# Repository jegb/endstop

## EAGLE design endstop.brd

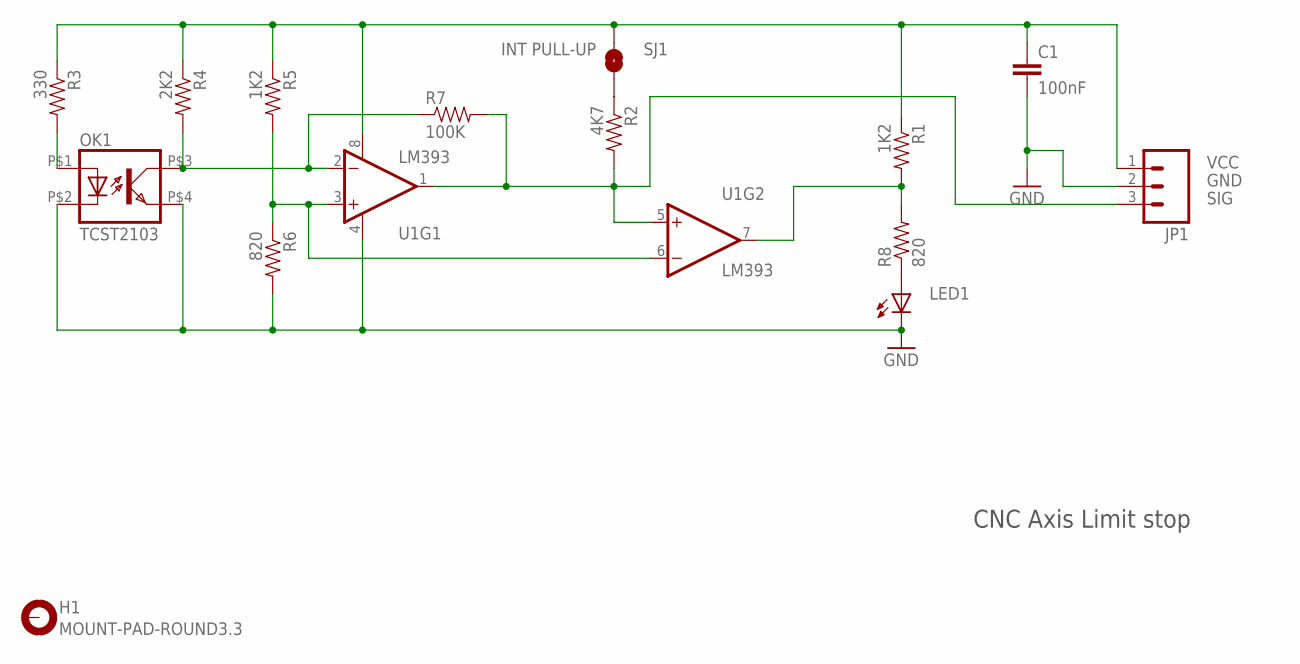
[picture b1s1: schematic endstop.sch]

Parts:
C1: 100nF; 0805
H1: MOUNT-PAD-ROUND3.3; 3,3-PAD
JP1: M03JST-PTH; JST-3-PTH
LED1: LED0603; LED-0603
OK1: TCST2103
R1, R5: 1K2; 0805
R2: 4K7; 0805
R3: 330; 0805
R4: 2K2; 0805
R6, R8: 820; 0805
R7: 100K; 0805
SJ1: INT PULL-UP; SJ_2S-NO
U1: LM393; SO08

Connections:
GND: C1.2, JP1.2, LED1.C, OK1.P$2 (C), OK1.P$4 (EMIT), R6.2, U1.4 (V-)
unnamed: R5.2, R6.1, U1.3 (+IN), U1.6 (-IN)
unnamed: OK1.P$3 (COL), R4.2, R7.1, U1.2 (-IN)
unnamed: R1.2, R8.2, U1.7 (OUT)
unnamed: OK1.P$1 (A), R3.2
unnamed: LED1.A, R8.1
unnamed: R2.1, SJ1.1
SIG: JP1.3, R2.2, R7.2, U1.1 (OUT), U1.5 (+IN)
VCC: C1.1, JP1.1, R1.1, R3.1, R4.1, R5.1, SJ1.2, U1.8 (V+)

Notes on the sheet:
CNC Axis Limit stop

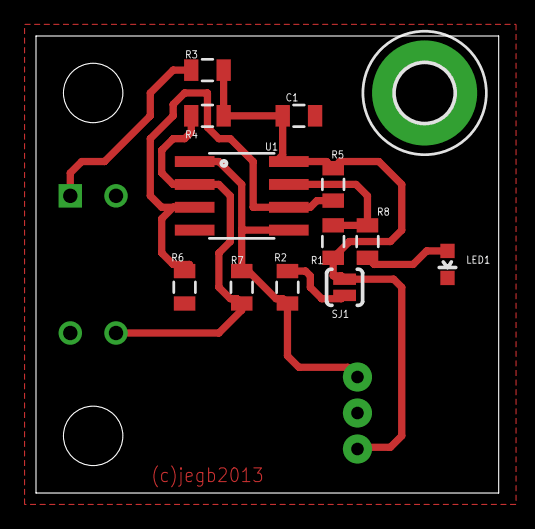
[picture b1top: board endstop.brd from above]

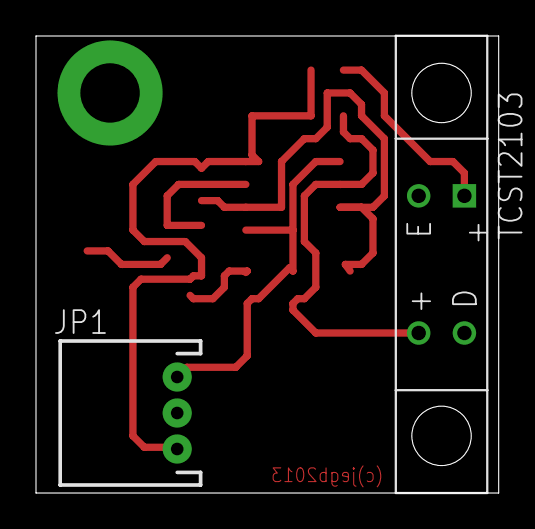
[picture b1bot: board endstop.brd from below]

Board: 2 copper layers, 25.7 x 25.4 mm, 15 parts (2 on the bottom side), 9 nets.

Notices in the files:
parts and their libraries:
SparkFun: Licensing: CC v3.0 Share-Alike You are welcome to use this library for commercial purposes.
